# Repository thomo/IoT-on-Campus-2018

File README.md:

Boards, sources and configuration to run the Mini-Hackathon at SQS Campus 2018.
The infrastructure consists of two kind of ESP8266 nodes - called NodeA and NodeB - and a master. The master is running on a Raspberry Pi 3. On the master a bundle of applications is installed:
- Mosquitto - a MQTT server
- Influxdb - a time based database
- Grafana 
- NodeRed

The NodeA/NodeB are small IoT devices with a temperature/humidity/pressure sensor, two switches and some RGB leds. While NodeA is prebuild and will be distributed on the campus location to collect sensor data the NodeB will be put together by the participants in a workshop.

## Setup Arduino for ESP8266

(Source: https://github.com/esp8266/Arduino)

- Install the current upstream Arduino IDE at the 1.8 level or later. The current version is at the Arduino website.
- Start Arduino and open Preferences window.
- Enter http://arduino.esp8266.com/stable/package_esp8266com_index.json into Additional Board Manager URLs field. You can add multiple URLs, separating them with commas.
- Open Boards Manager from Tools > Board menu and install esp8266 platform (and don't forget to select your ESP8266 board from Tools > Board menu after installation).

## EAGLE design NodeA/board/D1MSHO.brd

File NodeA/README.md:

# Circuit

A ESP8266 node with
- 2x WS2812A RGB LEDs, DIN on D5 (GPIO14)
- 2x switchs on D6 (GPIO12) and D7 (GPIO13) with 10k pull-ups
- 1x BME280, SCL on D1 (GPIO05) and SDL on D2 (GPIO04)

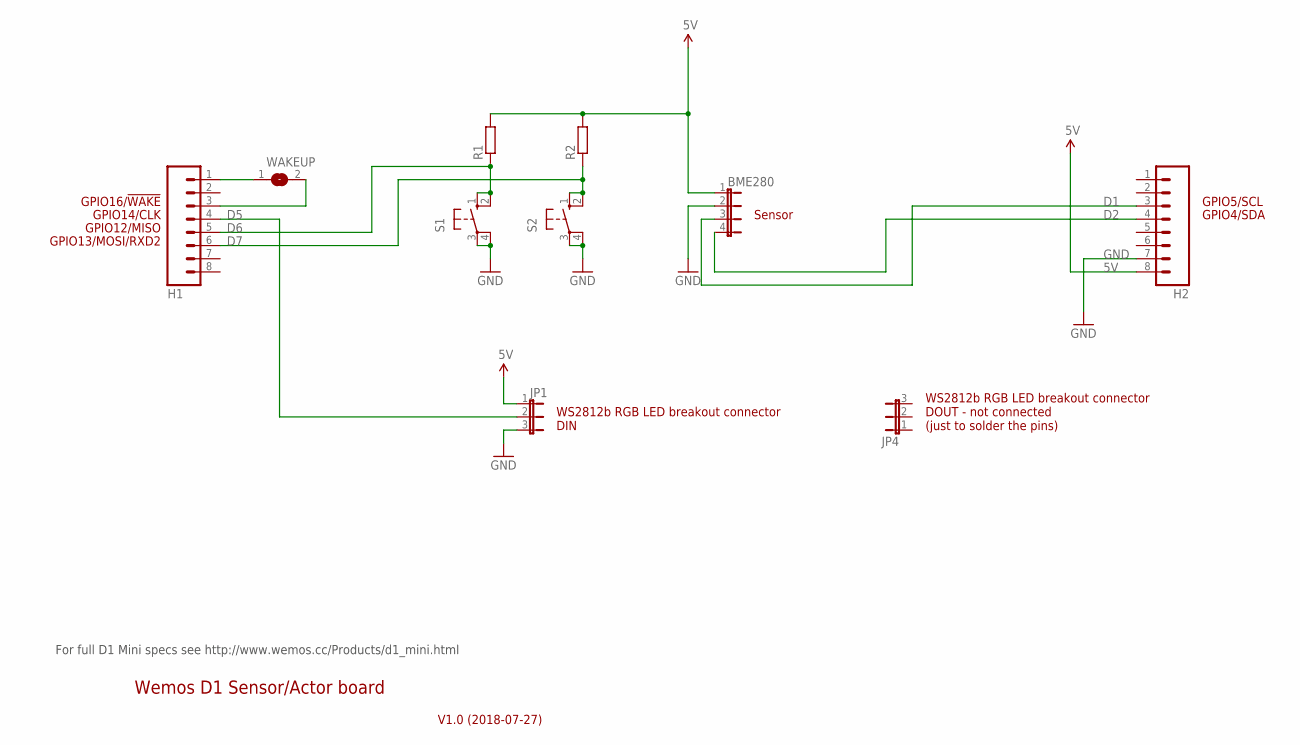
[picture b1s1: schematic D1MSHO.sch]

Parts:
BME280: JP4E; JP4
H1, H2: M08; 1X08
JP1, JP4: JP2E; JP2
R1, R2: R-EU_R0805; R0805
S1, S2: 10-XX; B3F-10XX
WAKEUP: SJ

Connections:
5V: BME280.1, H2.8, JP1.1, R1.2, R2.2
D1: BME280.3, H2.3
D2: BME280.4, H2.4
D5: H1.4, JP1.2
D6: H1.5, R1.1, S1.1 (S), S1.2 (S1)
D7: H1.6, R2.1, S2.1 (S), S2.2 (S1)
GND: BME280.2, H2.7, JP1.3, S1.3, S1.4 (P1), S2.3, S2.4 (P1)
unnamed: H1.1, WAKEUP.1
unnamed: H1.3, WAKEUP.2

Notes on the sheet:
GPIO12/MISO
GPIO4/SDA
GPIO5/SCL
GPIO13/MOSI/RXD2
GPIO14/CLK
GPIO16/!WAKE
V1.0 (2018-07-27)
For full D1 Mini specs see http://www.wemos.cc/Products/d1_mini.html
Wemos D1 Sensor/Actor board
WS2812b RGB LED breakout connector DIN
WS2812b RGB LED breakout connector DOUT - not connected (just to solder the pins)
Sensor

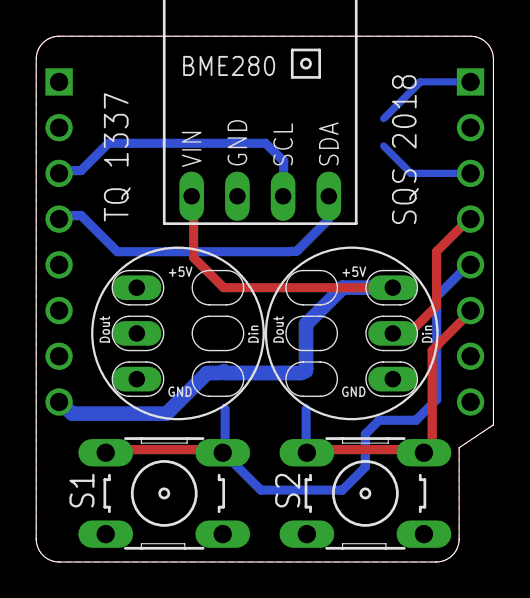
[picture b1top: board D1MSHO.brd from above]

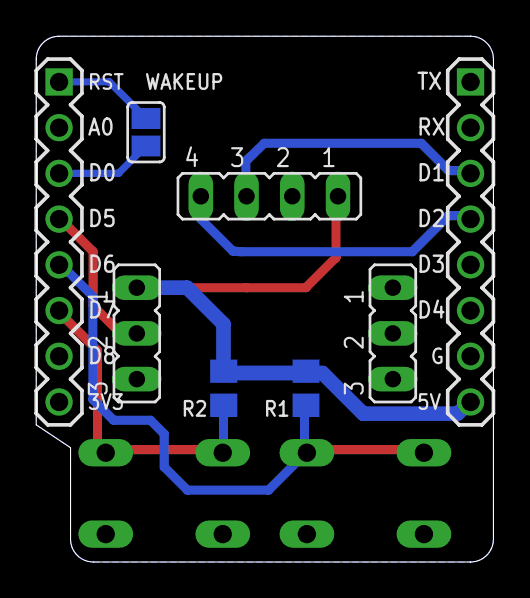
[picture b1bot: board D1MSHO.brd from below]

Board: 2 copper layers, 25.4 x 29.2 mm, 12 parts (8 on the bottom side), 9 nets.

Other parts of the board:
U$2, U$4: WS2812BBOARD

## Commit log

2018-07-09 init with NodeA
2018-07-09 add board images
2018-07-27 first bootstrap steps
2018-07-27 add bootstrap phase 2
2018-07-27 install mosquitto
2018-07-28 install influxdb and telegraf
2018-07-28 install grep as a base package
2018-07-28 ignore retry files
2018-07-28 ignore any retry file
2018-07-28 install nodered, grafana and nginx
2018-07-28 add reference to original install description
2018-07-28 fix markdown layout issue
2018-07-29 add predefined datasources to grafana
2018-07-29 create onenode playbook and extend docu
2018-08-05 set board name and export circuit
2018-08-05 move board files to sub dir
2018-08-05 program to test the node
2018-08-06 add notes about used libraries
2018-08-07 config mode for nodeA
2018-08-15 init version. connect to mqtt server; subscribe to topcs; do something if topics arrive
2018-08-15 init version. connect to mqtt server; publish topic with switch value each call
2018-08-15 move
2018-08-16 Schaltplan NodeB
2018-08-16 Program for testing the wiring of a NodeB
2018-08-17 short overview and notes about arduino setup
2018-08-17 init example; led ring switches from red, green, blue
2018-08-20 add comment with used libs
2018-08-20 init checkin of untested example. Buttons can be used to switch LEDs in Ring (left/right direction)
2018-08-20 init checkin of untested example. Buttons can be used to switch on the onboard LED
2018-08-21 remove new line after value for btn1
2018-08-21 add first version of session ppt
2018-08-24 change clientId to mac adress of node
2018-08-24 add parameter to WifiManager
2018-08-27 add (very) short MQTT and INFLUXDB intro
2018-08-28 add mqtt functionality
2018-08-28 pub/sub mqtt message
2018-08-29 added node red flow as json string
2018-08-29 added TQ_flow.json (for real now)
2018-08-30 fix color parsing
2018-08-30 fix payload processing
2018-08-30 add color picker to ui
2018-09-01 Alternative versions for NodeA and NodeRed NodeA: Loop handles now both button clicks separately and sending the to /campus/Button0 or /campus/Button1. callback function now reads either 1=r_g_b or n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
2018-09-03 add grafana slides
2018-09-03 init checkin of NodeA Infoblatt
2018-09-03 fix typo
2018-09-03 add slide with tasks for participants
2018-09-03 added Node-RED slide
2018-09-04 add LINK slide
2018-09-04 update docu pdf
2018-09-04 added more Node-RED slides
2018-09-04 some typo fixed
2018-09-05 add circuits to nodes and nodeA firmware description
2018-09-05 added rating flow for node red added rating functionality to nodeA
2018-09-06 remove leading slash in topic
2018-09-06 add WLAN and UI data
2018-09-06 publish button state and sub feedback topic
2018-09-06 add info about WLAN, IP and credentials
2018-09-06 added rating to TQ flow
2018-09-06 add like/dislike
2018-09-06 fix influxdb line
2018-09-06 fix mqtt topics
2018-09-06 final Node Red flow with evaluation

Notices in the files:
parts and their libraries:
freetronics-original: Licensing: CC v3.0 Share-Alike You are welcome to use this library for commercial purposes.
